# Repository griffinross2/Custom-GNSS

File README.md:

# Custom-GNSS
My work to create a custom FPGA GNSS receiver. This repository is to contain code for complete simulation and design of a multi-constellation GNSS receiver. The receiver will be built in hardware using a front-end digitizer module, an FPGA for demodulation and tracking with a soft CPU implemented on-chip, and a microcontroller for high-level computation and solving.

## Simulation
Directory with code used to simulate and test the receiver in software.

### TrackerSim
C++ Simulation of GNSS Recevier. To use, open in vscode and use the CMake file to build and run. A binary file with 1-bit I samples like [gnss-20170427-L1.1bit.I.bin](https://drive.google.com/file/d/158aSbdcyE3B8lAzl-4mJcwwZusJo11b2/view?usp=sharing) is required.

## Hardware
Directory with hardware design files.

### GNSS-board-v0
Initial GNSS receiver board design in KiCAD 9.

## Logs
General place for storing logs of simulation runs and other relevant test data.

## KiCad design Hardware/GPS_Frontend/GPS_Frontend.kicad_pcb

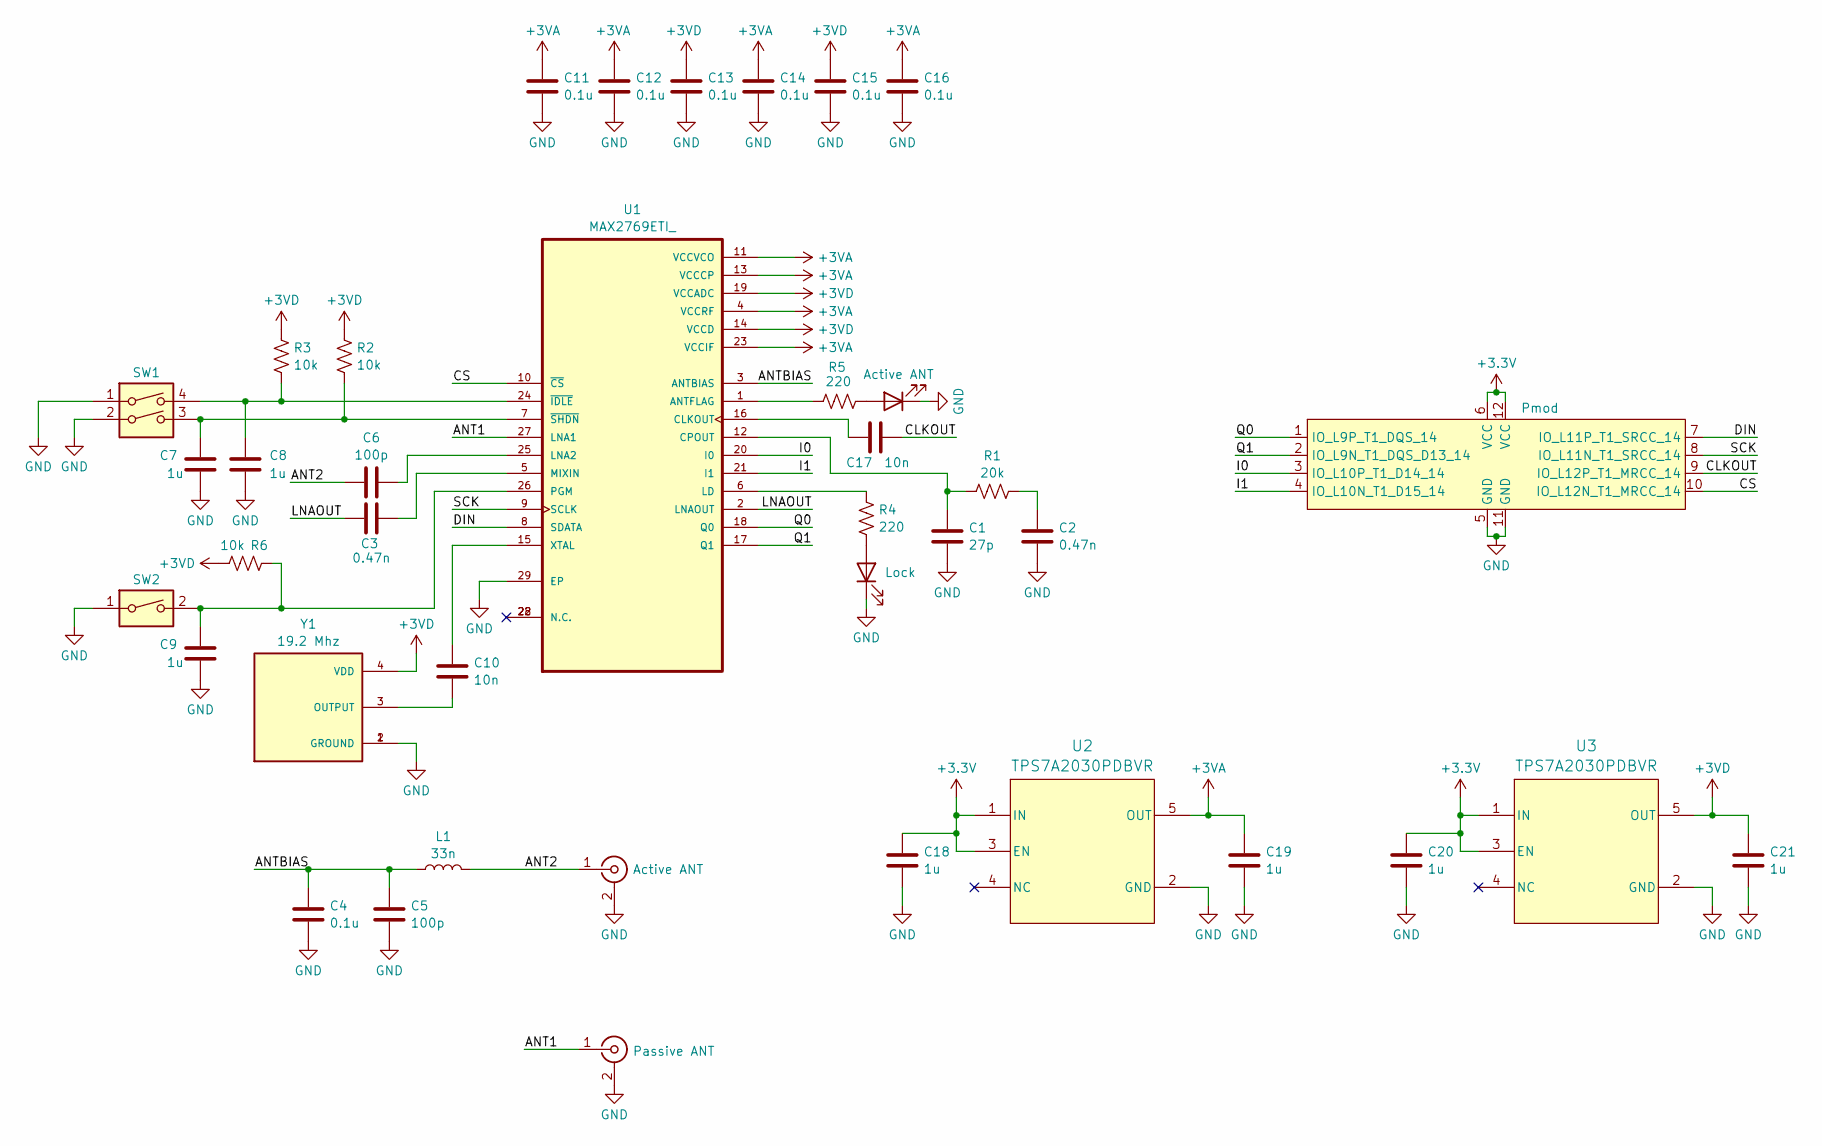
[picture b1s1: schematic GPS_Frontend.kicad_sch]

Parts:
C1: 27p; C_0402_1005Metric; Manufacturer_Part_Number GCM1555C1H270JA16J
C2, C3: 0.47n; C_0402_1005Metric; Manufacturer_Part_Number GCM1555C1H471JA16J
C4, C11, C12, C13, C14, C15, C16: 0.1u; C_0402_1005Metric; Manufacturer_Part_Number GRM155R61A104KA01J
C5, C6: 100p; C_0402_1005Metric; Manufacturer_Part_Number GRM1555C2A101GA01D
C7, C8, C9, C18, C19, C20, C21: 1u; C_0603_1608Metric; Manufacturer_Part_Number GRM188R61A105KA61J
C10, C17: 10n; C_0603_1608Metric; Manufacturer_Part_Number GCM188R72A103KA37D
J1: Pmod; PinHeader_2x06_P2.54mm_Horizontal_Pmod; Manufacturer_Part_Number HTSW-106-08-G-D-RA
J2: Passive ANT; SMA_Amphenol_132289_EdgeMount; Manufacturer_Part_Number 60312242114510
J3: Active ANT; SMA_Amphenol_132289_EdgeMount; Manufacturer_Part_Number 60312242114510
L1: 33n; L_0402_1005Metric; Manufacturer_Part_Number LQW15AN33NJ80D
LED1: Active ANT; LED_0805_2012Metric; Manufacturer_Part_Number 150080VS75000
LED2: Lock; LED_0805_2012Metric; Manufacturer_Part_Number 150080RS75000
R1: 20k; R_0603_1608Metric; Manufacturer_Part_Number RT0603FRE1020KL
R2, R3, R6: 10k; R_0603_1608Metric; Manufacturer_Part_Number RE0603FRE1310KL
R4, R5: 220; R_0603_1608Metric; Manufacturer_Part_Number RC0603JR-07220RP
SW1: SW_DIP_x02; SW_DIP_SPSTx02_Slide_6.7x6.64mm_W8.61mm_P2.54mm_LowProfile; Manufacturer_Part_Number A6S-2104-H
SW2: SW_DIP_x01; SW_DIP_SPSTx01_Slide_6.7x4.1mm_W8.61mm_P2.54mm_LowProfile; Manufacturer_Part_Number A6S-1104-H
U1: MAX2769ETI_; QFN50P500X500X80-29N; Manufacturer_Part_Number MAX2769ETI
U2, U3: TPS7A2030PDBVR; DBV0005A-IPC_A; Manufacturer_Part_Number TPS7A2030PDBVR
Y1: 19.2 Mhz; OSC_ECS-TXO-20CSMV4-192-AN-TR; PARTREV N/A

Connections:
+3.3V: C18.1, C20.1, J1.6 (VCC), J1.12 (VCC), U2.1 (IN), U2.3 (EN), U3.1 (IN), U3.3 (EN)
+3VA: C11.1, C12.1, C14.1, C16.1, C19.1, U1.4 (VCCRF), U1.11 (VCCVCO), U1.13 (VCCCP), U1.23 (VCCIF), U2.5 (OUT)
+3VD: C13.1, C15.1, C21.1, R2.1, R3.1, R6.1, U1.14 (VCCD), U1.19 (VCCADC), U3.5 (OUT), Y1.4 (VDD)
/ANT1: J2.1 (In), U1.27 (LNA1)
/ANT2: C6.1, J3.1 (In), L1.2
/ANTBIAS: C4.1, C5.1, L1.1, U1.3 (ANTBIAS)
/CLKOUT: C17.2, J1.9 (IO_L12P_T1_MRCC_14)
/CS: J1.10 (IO_L12N_T1_MRCC_14), U1.10 (~CS)
/DIN: J1.7 (IO_L11P_T1_SRCC_14), U1.8 (SDATA)
/I0: J1.3 (IO_L10P_T1_D14_14), U1.20 (I0)
/I1: J1.4 (IO_L10N_T1_D15_14), U1.21 (I1)
/LNAOUT: C3.1, U1.2 (LNAOUT)
/Q0: J1.1 (IO_L9P_T1_DQS_14), U1.18 (Q0)
/Q1: J1.2 (IO_L9N_T1_DQS_D13_14), U1.17 (Q1)
/SCK: J1.8 (IO_L11N_T1_SRCC_14), U1.9 (SCLK)
GND: C1.2, C2.2, C4.2, C5.2, C7.2, C8.2, C9.2, C11.2, C12.2, C13.2, C14.2, C15.2, C16.2, C18.2, C19.2, C20.2, C21.2, J1.5 (GND), J1.11 (GND), J2.2 (Ext), J3.2 (Ext), LED1.1 (K), LED2.1 (K), SW1.1, SW1.2, SW2.1, U1.29 (EP), U2.2 (GND), U3.2 (GND), Y1.1 (GROUND), Y1.2 (GROUND)
unnamed: C2.1, R1.2
unnamed: LED1.2 (A), R5.1
unnamed: LED2.2 (A), R4.1
unnamed: R5.2, U1.1 (ANTFLAG)
unnamed: C17.1, U1.16 (CLKOUT)
unnamed: C1.1, R1.1, U1.12 (CPOUT)
unnamed: R4.2, U1.6 (LD)
unnamed: C6.2, U1.25 (LNA2)
unnamed: C3.2, U1.5 (MIXIN)
unnamed: C9.1, R6.2, SW2.2, U1.26 (PGM)
unnamed: C10.1, U1.15 (XTAL)
unnamed: C8.1, R3.2, SW1.4, U1.24 (~IDLE)
unnamed: C7.1, R2.2, SW1.3, U1.7 (~SHDN)
unnamed: C10.2, Y1.3 (OUTPUT)

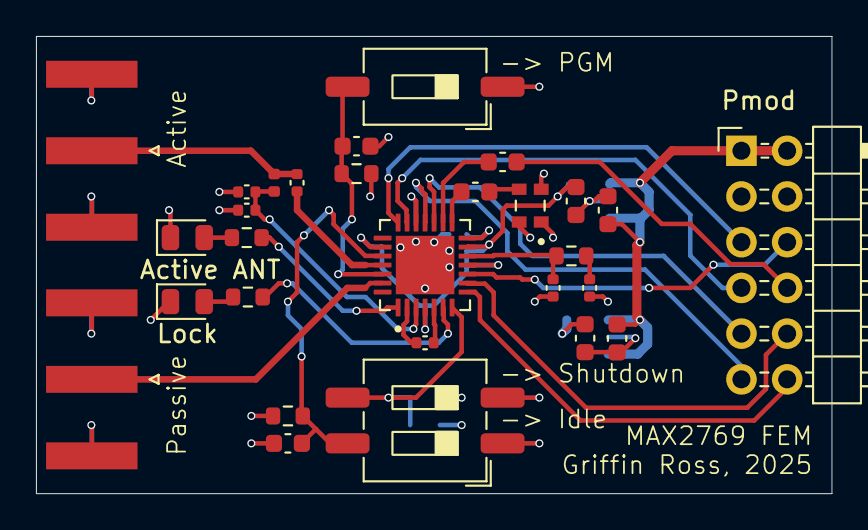
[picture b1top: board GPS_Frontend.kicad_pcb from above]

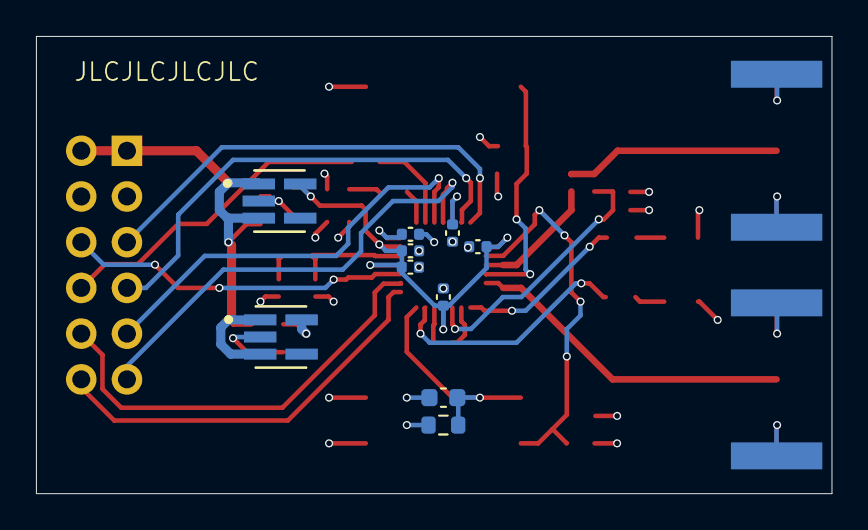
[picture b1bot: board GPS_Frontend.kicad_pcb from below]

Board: 4 copper layers, 44.2 x 25.4 mm, 39 parts (10 on the bottom side), 30 nets.

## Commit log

2025-01-02 Started writing signal simulator
2025-01-02 C code to generate and acquire galileo
2025-01-03 Rewrites to support multiple signals, write acquisition functions
2025-01-06 Basic tracking for L1CA and E1, E1 not fully working
2025-01-11 More robust E1 tracking, L1/E1 nav decoding, ephemeris
2025-01-11 Position solution, individual and combined systems
2025-02-17 Add acquisition function for WAAS
2025-02-24 Track WAAS (just demodulation)
2025-02-24 Continued to develop WAAS tracker
2025-02-27 Add empty kicad project
2025-03-06 Add FFTW3 licenses
2025-03-06 Create LICENSE
2025-03-07 Update LICENSE
2025-04-19 L1CA code generator RTL
2025-04-19 L1CA channel and testbench
2025-04-19 Add frontend board design to Hardware
2025-04-20 Version submitted for manufacturing
2025-04-24 Squashed 'RTL/temp/' content from commit af3411a
    git-subtree-dir: RTL/temp
    git-subtree-split: af3411ab263d042fedef24a006a7f5a3c6fd4877
2025-04-24 Add AHB satellite for GNSS
2025-05-18 Wrote code to record data from the MAX2769 frontend
2025-05-20 L1 C/A search
2025-05-20 dumb
2025-05-21 :facepalm:
2025-05-23 Smaller, simpler multiplier for search
2025-05-23 Reduce unnecessarily large bitwidths
2025-05-24 Create fine search module
    Taking course acquisition results, resolves the phase to 1/8 chip increments, and doppler to 50Hz increments.
    - Tentatively, want to implement into fully automated system without CPU intervention. Will need to accommodate for phase differences between sampling in each stage of acquisition and initialization 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
2025-05-30 Update CPU and implement test of acqusition
    The coarse acquisition works, but the compensation for code slippage is not accurate enough. Its also slow. I want to rethink the whole strategy and try a hardware FFT approach (AC-PCA using FFTs loo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
2025-09-26 RTL changes I apparently forgot, plus add in fftw3
2025-09-26 License has to change because of GPL in FFTW3
    Booooo
